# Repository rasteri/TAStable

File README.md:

# TAStable
Deliciously synchronizing the SNES' APU to its CPU clock

## Background
With few exceptions, Tool Assisted Speedruns are rigid lists of controller inputs that have no way to adapt to changing circumstances, and so require the game console to behave in a completely deterministic manner.

Many consoles - ones that drive their logic synchronously from a single master clock - behave more-or-less identically each time they are reset, and so are relatively simple to design speedruns for.

The SNES throws a spanner in the works by having its audio subsystem run from a separate clock. This secondary clock runs completely asynchronously to the main CPU clock, and in fact is derived from a very imprecise source (ceramic resonator). This plus a very non-deterministic reset circuit makes the SNES a difficult moving target for tool assisted speedruns to hit.

Workarounds such as latch trains have been found that increase reliability for certain games, but there are many others which just refuse to sync.

So we decided to just cheat and modify the console instead.

## Theory

NOTE - All of this applies to the 3chip snes (specifically the shvc-cpu-01 with SHVC-sound module) and may or may not be adaptable to other models.

### Terms - 
CPU - the main 65816 processor in the SNES

PPU1/PPU2 - the Picture Processing Units that generate graphics

APU - Audio Processing Unit, actually comprised of two processors - the SMP and DSP.

### Clock Domain Synchronizing

The SNES has two clock domains that are derived from two discrete non-synchronized oscillators. To have a hope of making the SNES deterministic, we have to derive these clocks from a common source.

Clock domain one is derived from a crystal and runs at 21.4773MHz (fraction 945/44). It directly clocks the CPU as well as PPU1 and PPU2.

Clock domain two is derived from a ceramic resonator and runs at 24.576MHz (29×48 kHz). It directly clocks the DSP, which in turn divides it by 12* and clocks the SMP.

*(During startup the DSP actually clocks the SMP at 1.024MHz for a while, presumably to synchronize the DSP and SMP’s memory read cycles, which we’ll go into later)

The ratio of the CPU clock to the APU clock is exactly 39375/45056, but that’s a little tricky to achieve in a low-cost FPGA. However a ratio of 7/8 is easier to implement and is close enough, in fact well within the tolerance of the ceramic resonator, so this ratio was decided upon.

Some simple FPGA code was written to generate a master 171.8184MHz clock. This is then divided by 7 to get a 24.55MHz APU clock, and divided by 8 to get a 21.4773MHz CPU clock.

Just deriving the clocks from a common source was good enough to make at least one game (Donkey Kong Country 2) “deterministic enough” to complete reliably - although it still required other workarounds (latch trains) to compensate for the remaining nondeterminism. Other games (Super Metroid) were still proving impossible to sync, so the decision was taken to track down every other source of nondeterminism come hell or high water.

### Reset Sequencing

The reset arrangement in the SNES looks like this : 

Net names are from the “snes_schematic_color.pdf” that’s floating around.

There are a number of ways the SNES can be reset. 

* Turning it on. The CIC will reset the PPU and the PST529 will reset the CPU/DSP/SMP. The PST529 takes a different amount of time to reset each time the SNES is switched on.
* Pressing the reset switch. The CIC will reset PPU2, which will in turn reset all the other components. As the CPU and APU’s resets are connected through a 1K resistor, this causes the signal to rise slowly and thus be susceptible to noise and other factors.
* Pull RESOUT1 low using external circuitry. This is often done to automate TAS playback, as the signal is accessible on the cartridge and expansion ports. This resets the CPU and DSP, but unfortunately doesn’t reset the PPU so leaves it in an unknown state.

None of these approaches allow the reset signal to trigger all ICs simultaneously. Luckily the solution is simple : 

If RESOUT1 and RESET are connected together, all ICs are reset simultaneously (or at least, in a repeatable fashion).

There may be a better way to do this (maybe just shorting R74?)

### Reset Timing

This is still not enough to guarantee fully deterministic behavior, as with this setup we aren’t controlling the exact timing of the reset signal itself. Thus, the reset signal might happen at ANY point in the 21MHz/24MHz “synchronization cycle” - and there are infinite possibilities.

The “synchronization cycle” is equivalent to the beat frequency of the two clocks - i.e. 3MHz. So to ensure that the systems start up the same way each time, we have to ensure that the reset signal comes at the same point in the beat frequency on each reset.

To do this we can generate a third clock from the master 171.8184MHz clock, with a divider of 56, and reset the CPU/APU/PPUs on its rising (or falling) edge. As long as all three clocks are kept in the same phase, the reset signal will always happen at the same time in the clock sequence, and should guarantee determinism.

But, infuriatingly, even synchronizing the reset signal to the clock phase still doesn’t make the console 100% deterministic. It lowers the number of “different behaviour patterns” to about 20, so we know we’re going in the right direction, but there is still one more piece of the puzzle.

### Memory Bus Sniffing

The final piece of nondeterminism comes from the APU. As mentioned before, the DSP generates the SMP’s 2MHz clock by dividing the 24MHz clock. Unfortunately, the internal counters that the DSP uses to derive that clock are reset to a random state when the console powers up, and there is (probably?) no way to reset them back to zero. So, we need to find another way to determine where the APU is in its operation cycle.

When the APU starts up, it performs a number of read operations on its memory bus, followed by a memory write. After that point it appears to stabilize, i.e. it behaves deterministically. So if we can delay starting the CPU until after the first APU memory write, this will synchronize the two:

(Note, when it says “some (exact) time later”, this can be an arbitrary amount of time, but it should be carefully controlled to ensure it is reproducible. In addition, there appear to be certain values of time that do NOT result in deterministic behavior, presumably because it is too close to a clock transition or because it requires the clock to be high (or low) when the devices are brought out of reset.)

This requires separating the RESOUT1 signal into two sections, one for the CPU and one for the APU, and resetting them separately (APU first, then CPU after the APU stabilizes) :

This approach still doesn't appear to make the snes fully deterministic, but that may be enough to sync runs that previously wouldn't.

More research will be done when I've finished moving house and I have access to my logic analyzer again

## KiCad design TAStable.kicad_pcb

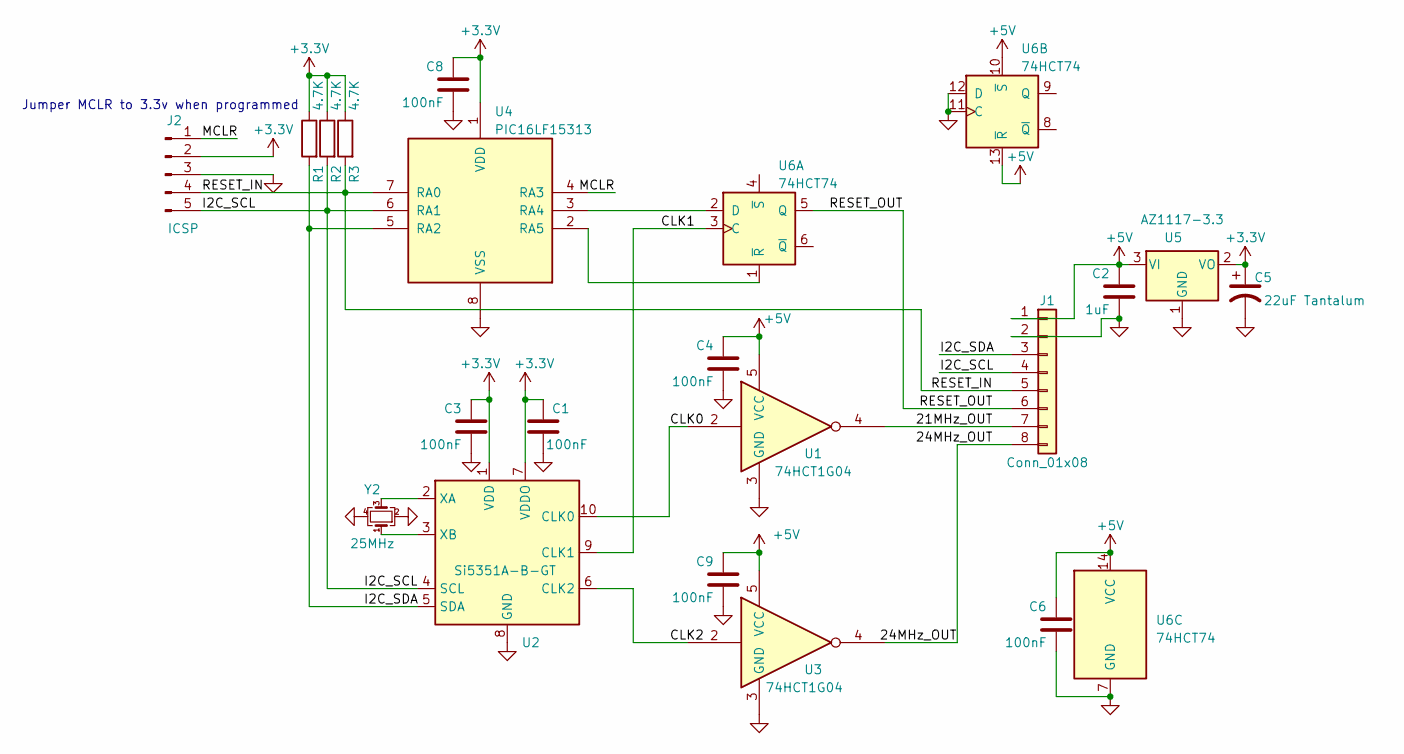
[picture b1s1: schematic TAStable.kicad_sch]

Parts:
C1, C3, C4, C6, C8, C9: 100nF; C_0603_1608Metric
C2: 1uF; C_0603_1608Metric
C5: 22uF Tantalum; C_1206_3216Metric
J1: Conn_01x08; PinHeader_1x08_P2.54mm_Vertical
J2: ICSP; PinSocket_1x05_P2.54mm_Vertical
R1, R2, R3: 4.7K; R_0603_1608Metric
U1, U3: 74HCT1G04; SOT-353_SC-70-5
U2: Si5351A-B-GT; MSOP-10_3x3mm_P0.5mm
U4: PIC16LF15313; SOIC-8_3.9x4.9mm_P1.27mm
U5: AZ1117-3.3; SOT-89-3
U6: 74HCT74; TSSOP-14_4.4x5mm_P0.65mm
Y2: 25MHz; Crystal_SMD_Abracon_ABM8G-4Pin_3.2x2.5mm

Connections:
+3.3V: C1.1, C3.1, C5.1, C8.1, J2.2, R1.1, R2.1, R3.1, U2.1 (VDD), U2.7 (VDDO), U4.1 (VDD), U5.2 (VO)
+5V: C2.1, C4.1, C6.1, C9.1, J1.1, U1.5 (VCC), U3.5 (VCC), U5.3 (VI), U6.10 (~S), U6.13 (~R), U6.14 (VCC)
/21MHz_OUT: J1.7, U1.4
/24MHz_OUT: J1.8, U3.4
/CLK0: U1.2, U2.10 (CLK0)
/CLK1: U2.9 (CLK1), U6.3 (C)
/CLK2: U2.6 (CLK2), U3.2
/I2C_SCL: J1.4, J2.5, R2.2, U2.4 (SCL), U4.6 (RA1)
/I2C_SDA: J1.3, R1.2, U2.5 (SDA), U4.5 (RA2)
/MCLR: J2.1, U4.4 (RA3)
/RESET_IN: J1.5, J2.4, R3.2, U4.7 (RA0)
/RESET_OUT: J1.6, U6.5 (Q)
GND: C1.2, C2.2, C3.2, C4.2, C5.2, C6.2, C8.2, C9.2, J1.2, J2.3, U1.3 (GND), U2.8 (GND), U3.3 (GND), U4.8 (VSS), U5.1 (GND), U6.7 (GND), U6.11 (C), U6.12 (D), Y2.2, Y2.4
unnamed: U2.2 (XA), Y2.3
unnamed: U2.3 (XB), Y2.1
unnamed: U4.3 (RA4), U6.2 (D)
unnamed: U4.2 (RA5), U6.1 (~R)

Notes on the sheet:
Jumper MCLR to 3.3v when programmed

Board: 2 copper layers, 20 parts (0 on the bottom side), 17 nets, no tracks yet.

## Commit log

2023-07-10 schematic
2023-07-10 cleanups
2023-07-10 Ratio setting script
2023-07-10 added board img
2023-08-17 code!
2023-08-17 5v output buffer
2023-08-17 i2c slave updates
2023-08-29 Board pic
2023-08-31 more pics + cleanups
2023-09-01 cleanup
2023-09-06 new ratio scripts
2023-09-06 speclling
2023-10-15 bummy bum bums
2023-10-16 fixes
2023-11-08 andy finally learns FPGA programming
2023-11-10 arbitrary ratio clocks
2023-11-12 oh dear it doesn't really work
2023-11-12 added rest of bloody files
2023-11-13 buh-roken
2023-12-30 more flexible reset
2024-01-11 back to old style
2024-01-12 new style with phase adjust
2024-01-17 new stuff
2024-02-15 gwrgerg
2024-02-15 added test rom
